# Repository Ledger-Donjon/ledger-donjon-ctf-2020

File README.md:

## Ledger Donjon CTF 2020

This repository lists most of the challenges created for Ledger Donjon CTF 2020.

**This repository will be updated in the next few weeks to add more challenges.**

More information about this CTF can be found on the
[website](https://donjon-ctf.io/). The scoreboard and additional writeups are
available on [CTF Time](https://ctftime.org/event/1173).

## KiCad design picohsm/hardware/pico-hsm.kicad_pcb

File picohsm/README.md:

# picoHSM

## Building and flashing the STM32F205

The firmware for the STM32F205 can be built using CMake:

    cd firmware-mcu
    mkdir build && cd build
    cmake ../src
    make

To flash the microcontroller, be sure the jumpers on the board are configured
properly (JP1 and JP2 on the left), then run:

    make flash

This will flash the board with the default IP and MAC addresses. Other firmwares
with alternate IP and MAC are built by CMake and can be flashed as well:

    make flash11  # For IP ending in .11

## Building and flashing the ATMEGA1284P

The firmware for the ATMEGA1284P can be built using CMake:

    cd firmware-sec
    mkdir build && cd build
    cmake ../src
    make

To flash the microcontroller, connect the Atmel-ICE programmer to the ISP6
connector, and run:

    make flash
    make fuses

Flashing the fuse is important: it configures the microcontroller to use an
external clock (here the clock generated by the STM32F205), which is important
for the third challenge.

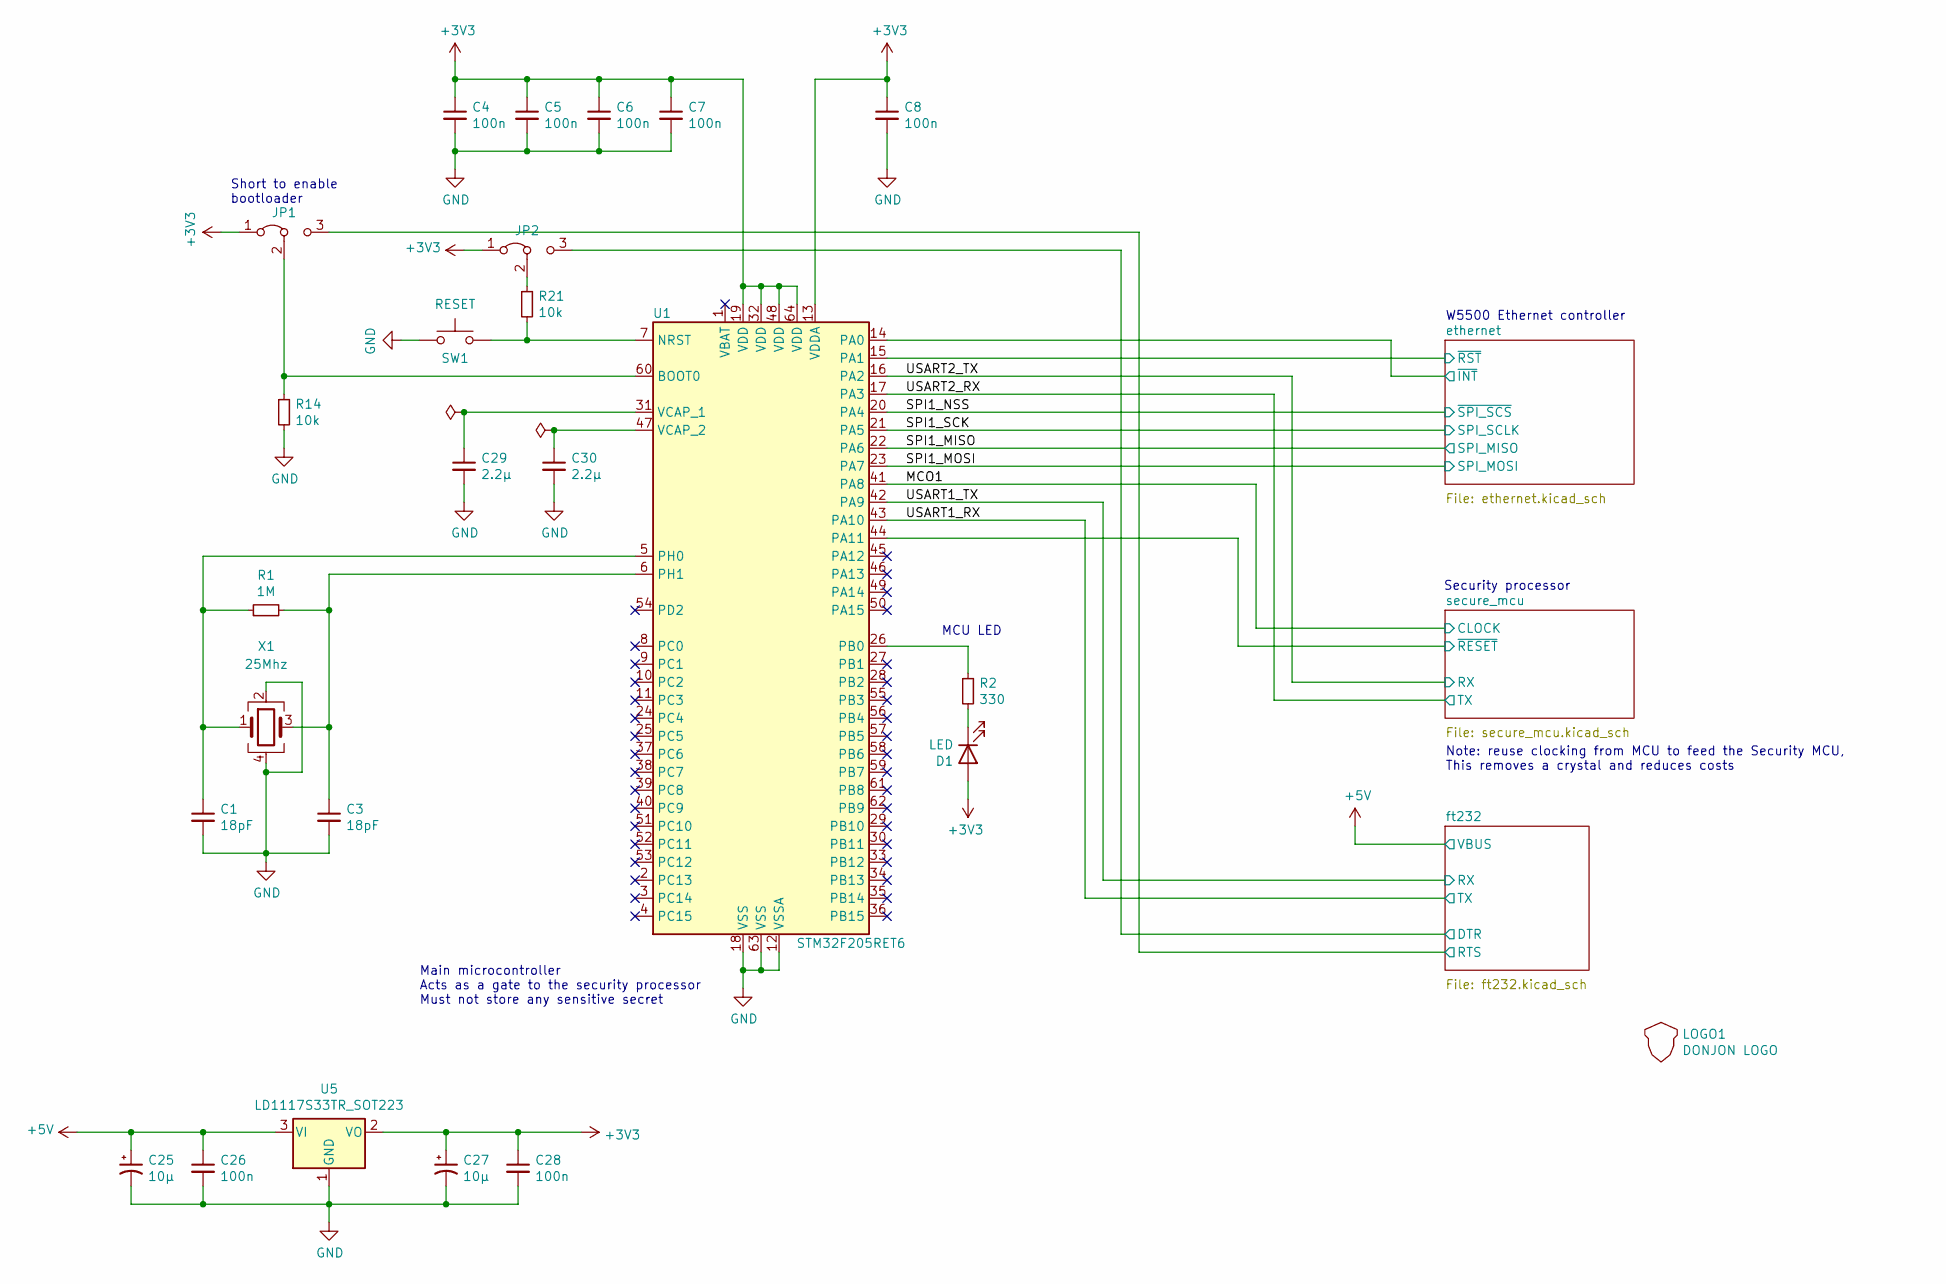
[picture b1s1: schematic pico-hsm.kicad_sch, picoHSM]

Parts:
C1, C3: 18pF; C_0603_1608Metric
C4, C5, C6, C7, C8, C26, C28: 100n; C_0603_1608Metric
C25, C27: 10µ; CP_EIA-3216-10_Kemet-I
C29, C30: 2.2µ; C_0603_1608Metric
D1: LED; D_0603_1608Metric
JP1, JP2: Jumper_3_Bridged12; PinHeader_1x03_P2.54mm_Vertical
LOGO1: DONJON LOGO; donjon-3000
R1: 1M; R_0603_1608Metric
R2: 330; R_0603_1608Metric
R14, R21: 10k; R_0603_1608Metric
SW1: RESET; SW_SPST_B3SL-1022P
U1: STM32F205RET6; LQFP-64_10x10mm_P0.5mm
U5: LD1117S33TR_SOT223; SOT-223-3_TabPin2
X1: 25Mhz; Crystal_SMD_5032-4Pin_5.0x3.2mm

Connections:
+3V3: C4.1, C5.1, C6.1, C7.1, C8.1, C27.1, C28.1, D1.2 (A), JP1.1 (A), JP2.1 (A), U1.13 (VDDA), U1.19 (VDD), U1.32 (VDD), U1.48 (VDD), U1.64 (VDD), U5.2 (VO); also elsewhere on the board
+5V: C25.1, C26.1, U5.3 (VI); also elsewhere on the board
/DTR: JP2.3 (B); also elsewhere on the board
/MCO1: U1.41 (PA8); also elsewhere on the board
/RTS: JP1.3 (B); also elsewhere on the board
/SPI1_MISO: U1.22 (PA6); also elsewhere on the board
/SPI1_MOSI: U1.23 (PA7); also elsewhere on the board
/SPI1_NSS: U1.20 (PA4); also elsewhere on the board
/SPI1_SCK: U1.21 (PA5); also elsewhere on the board
/USART1_RX: U1.43 (PA10); also elsewhere on the board
/USART1_TX: U1.42 (PA9); also elsewhere on the board
/USART2_RX: U1.17 (PA3); also elsewhere on the board
/USART2_TX: U1.16 (PA2); also elsewhere on the board
/~INT: U1.14 (PA0); also elsewhere on the board
/~RESET: U1.44 (PA11); also elsewhere on the board
/~RST: U1.15 (PA1); also elsewhere on the board
GND: C1.2, C3.2, C4.2, C5.2, C6.2, C7.2, C8.2, C25.2, C26.2, C27.2, C28.2, C29.2, C30.2, R14.2, SW1.1, U1.12 (VSSA), U1.18 (VSS), U1.63 (VSS), U5.1 (GND), X1.2, X1.4; also elsewhere on the board
unnamed: C1.1, R1.1, U1.5 (PH0), X1.1
unnamed: C3.1, R1.2, U1.6 (PH1), X1.3
unnamed: C29.1, U1.31 (VCAP_1)
unnamed: C30.1, U1.47 (VCAP_2)
unnamed: D1.1 (K), R2.2
unnamed: JP1.2 (C), R14.1, U1.60 (BOOT0)
unnamed: JP2.2 (C), R21.1
unnamed: R2.1, U1.26 (PB0)
unnamed: R21.2, SW1.2, U1.7 (NRST)

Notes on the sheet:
Short to enable bootloader
Main microcontroller Acts as a gate to the security processor Must not store any sensitive secret
MCU LED
W5500 Ethernet controller
Note: reuse clocking from MCU to feed the Security MCU, This removes a crystal and reduces costs
Security processor

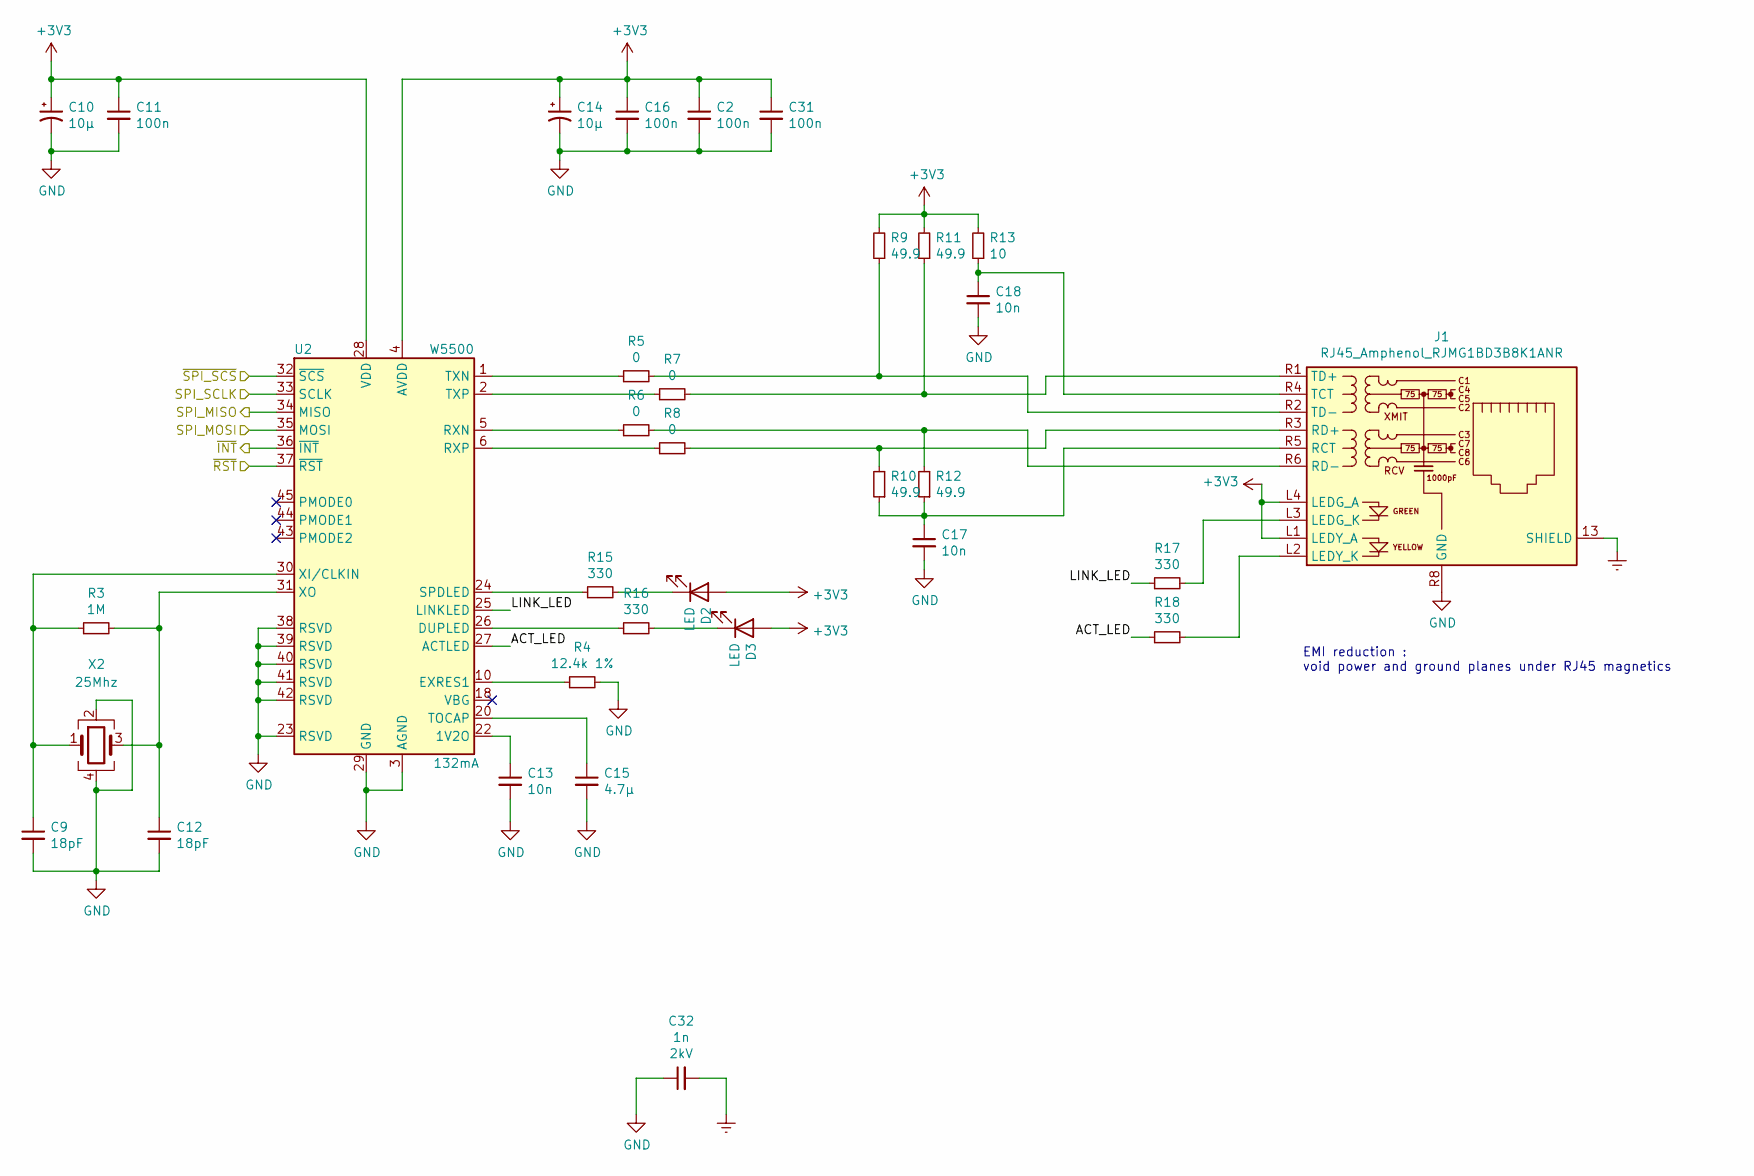
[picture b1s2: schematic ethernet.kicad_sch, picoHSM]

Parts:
C2, C11, C16, C31: 100n; C_0603_1608Metric
C9, C12: 18pF; C_0603_1608Metric
C10, C14: 10µ; CP_EIA-3216-10_Kemet-I
C13, C17, C18: 10n; C_0603_1608Metric
C15: 4.7µ; C_0603_1608Metric
C32: 1n; C_1206_3216Metric_Pad1.42x1.75mm_HandSolder; Voltage 2kV
D2, D3: LED; D_0603_1608Metric
J1: RJ45_Amphenol_RJMG1BD3B8K1ANR
R3: 1M; R_0603_1608Metric
R4: 12.4k 1%; R_0603_1608Metric
R5, R6, R7, R8: 0; R_0603_1608Metric
R9, R10, R11, R12: 49.9; R_0603_1608Metric
R13: 10; R_0603_1608Metric
R15, R16, R17, R18: 330; R_0603_1608Metric
U2: W5500; LQFP-48_7x7mm_P0.5mm
X2: 25Mhz; Crystal_SMD_5032-4Pin_5.0x3.2mm

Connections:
+3V3: C2.1, C10.1, C11.1, C14.1, C16.1, C31.1, D2.2 (A), D3.2 (A), J1.L1 (LEDY_A), J1.L4 (LEDG_A), R9.2, R11.2, R13.2, U2.4 (AVDD), U2.8 (AVDD), U2.11 (AVDD), U2.15 (AVDD), U2.17 (AVDD), U2.21 (AVDD), U2.28 (VDD); also elsewhere on the board
/SPI1_MISO: U2.34 (MISO); also elsewhere on the board
/SPI1_MOSI: U2.35 (MOSI); also elsewhere on the board
/SPI1_NSS: U2.32 (~SCS); also elsewhere on the board
/SPI1_SCK: U2.33 (SCLK); also elsewhere on the board
/ethernet/ACT_LED: R18.1, U2.27 (ACTLED)
/ethernet/LINK_LED: R17.1, U2.25 (LINKLED)
/~INT: U2.36 (~INT); also elsewhere on the board
/~RST: U2.37 (~RST); also elsewhere on the board
Earth: C32.2, J1.13 (SHIELD)
GND: C2.2, C9.2, C10.2, C11.2, C12.2, C13.2, C14.2, C15.2, C16.2, C17.2, C18.2, C31.2, C32.1, J1.R8 (GND), R4.2, U2.3 (AGND), U2.9 (AGND), U2.14 (AGND), U2.16 (AGND), U2.19 (AGND), U2.23 (RSVD), U2.29 (GND), U2.38 (RSVD), U2.39 (RSVD), U2.40 (RSVD), U2.41 (RSVD), U2.42 (RSVD), U2.48 (AGND), X2.2, X2.4; also elsewhere on the board
unnamed: C9.1, R3.1, U2.30 (XI/CLKIN), X2.1
unnamed: C12.1, R3.2, U2.31 (XO), X2.3
unnamed: C13.1, U2.22 (1V2O)
unnamed: C15.1, U2.20 (TOCAP)
unnamed: C17.1, J1.R5 (RCT), R10.1, R12.1
unnamed: C18.1, J1.R4 (TCT), R13.1
unnamed: D2.1 (K), R15.2
unnamed: D3.1 (K), R16.2
unnamed: J1.L2 (LEDY_K), R18.2
unnamed: J1.L3 (LEDG_K), R17.2
unnamed: J1.R1 (TD+), R7.2, R11.1
unnamed: J1.R2 (TD-), R5.2, R9.1
unnamed: J1.R3 (RD+), R8.2, R10.2
unnamed: J1.R6 (RD-), R6.2, R12.2
unnamed: R4.1, U2.10 (EXRES1)
unnamed: R5.1, U2.1 (TXN)
unnamed: R6.1, U2.5 (RXN)
unnamed: R7.1, U2.2 (TXP)
unnamed: R8.1, U2.6 (RXP)
unnamed: R15.1, U2.24 (SPDLED)
unnamed: R16.1, U2.26 (DUPLED)

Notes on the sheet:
EMI reduction : void power and ground planes under RJ45 magnetics

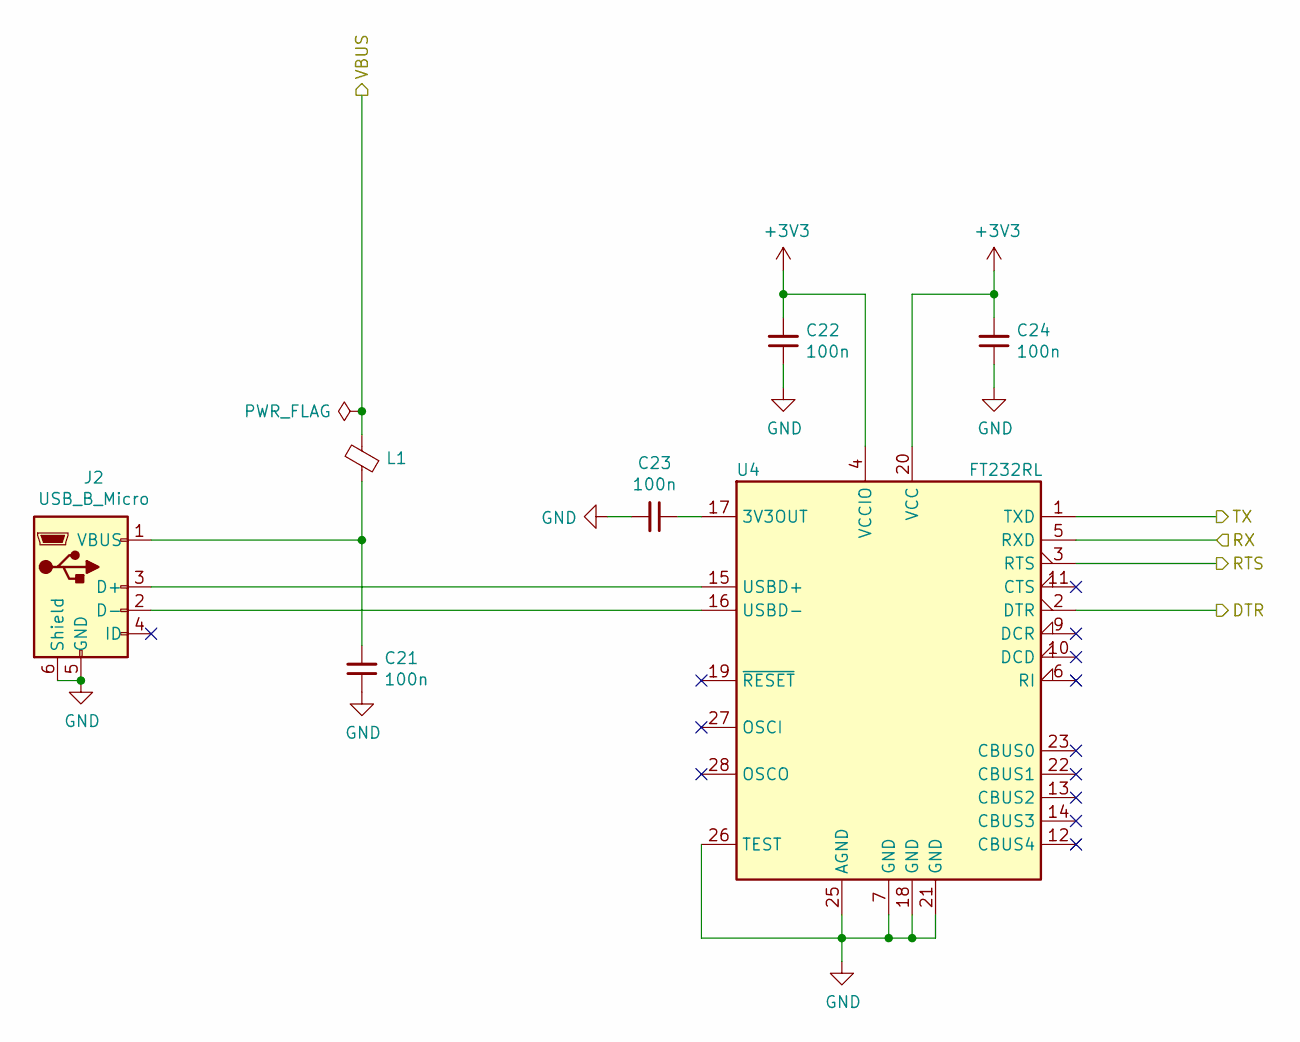
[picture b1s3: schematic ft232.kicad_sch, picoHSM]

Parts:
C21, C22, C23, C24: 100n; C_0603_1608Metric
J2: USB_B_Micro; USB_Micro-B_Wuerth_629105150521
L1: Ferrite_Bead_Small; L_0603_1608Metric
U4: FT232RL; SSOP-28_5.3x10.2mm_P0.65mm

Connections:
+3V3: C22.2, C24.2, U4.4 (VCCIO), U4.20 (VCC); also elsewhere on the board
+5V: L1.2; also elsewhere on the board
/DTR: U4.2 (DTR); also elsewhere on the board
/RTS: U4.3 (RTS); also elsewhere on the board
/USART1_RX: U4.1 (TXD); also elsewhere on the board
/USART1_TX: U4.5 (RXD); also elsewhere on the board
GND: C21.1, C22.1, C23.2, C24.1, J2.5 (GND), J2.6 (Shield), U4.7 (GND), U4.18 (GND), U4.21 (GND), U4.25 (AGND), U4.26 (TEST); also elsewhere on the board
unnamed: C21.2, J2.1 (VBUS), L1.1
unnamed: C23.1, U4.17 (3V3OUT)
unnamed: J2.2 (D-), U4.16 (USBD-)
unnamed: J2.3 (D+), U4.15 (USBD+)

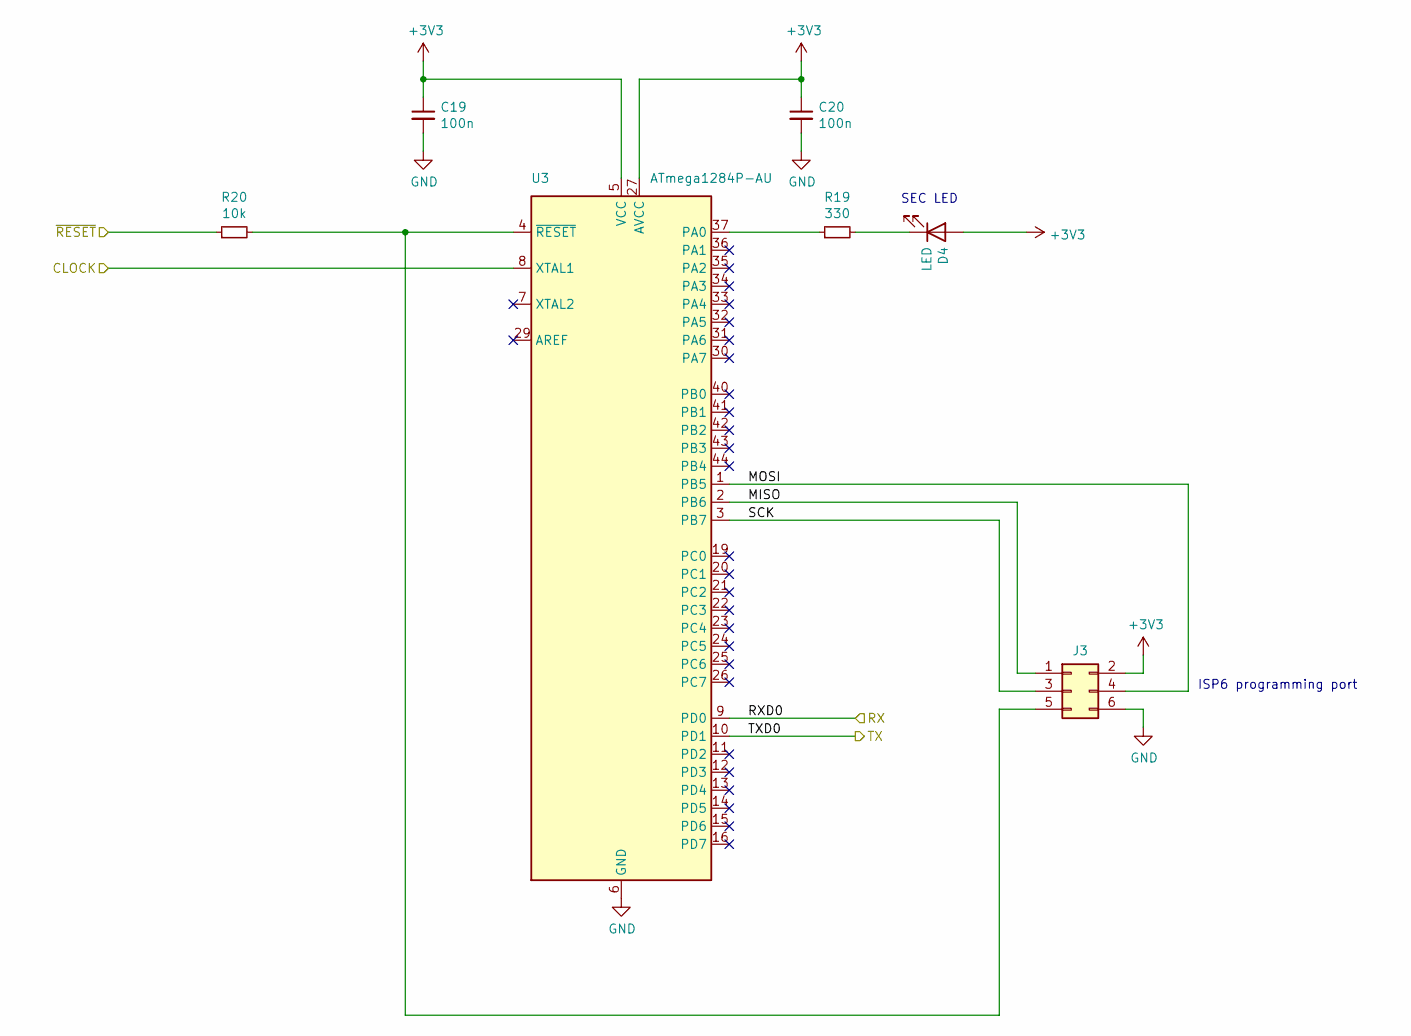
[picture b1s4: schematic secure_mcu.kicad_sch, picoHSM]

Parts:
C19, C20: 100n; C_0603_1608Metric
D4: LED; D_0603_1608Metric
J3: Conn_02x03_Odd_Even; PinHeader_2x03_P2.54mm_Vertical
R19: 330; R_0603_1608Metric
R20: 10k; R_0603_1608Metric
U3: ATmega1284P-AU; TQFP-44_10x10mm_P0.8mm

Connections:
+3V3: C19.1, C20.1, D4.2 (A), J3.2, U3.5 (VCC), U3.17 (VCC), U3.27 (AVCC), U3.38 (VCC); also elsewhere on the board
/MCO1: U3.8 (XTAL1); also elsewhere on the board
/USART2_RX: U3.10 (PD1); also elsewhere on the board
/USART2_TX: U3.9 (PD0); also elsewhere on the board
/secure_mcu/MISO: J3.1, U3.2 (PB6)
/secure_mcu/MOSI: J3.4, U3.1 (PB5)
/secure_mcu/SCK: J3.3, U3.3 (PB7)
/~RESET: R20.1; also elsewhere on the board
GND: C19.2, C20.2, J3.6, U3.6 (GND), U3.18 (GND), U3.28 (GND), U3.39 (GND); also elsewhere on the board
unnamed: D4.1 (K), R19.2
unnamed: J3.5, R20.2, U3.4 (~RESET)
unnamed: R19.1, U3.37 (PA0)

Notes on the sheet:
SEC LED
ISP6 programming port

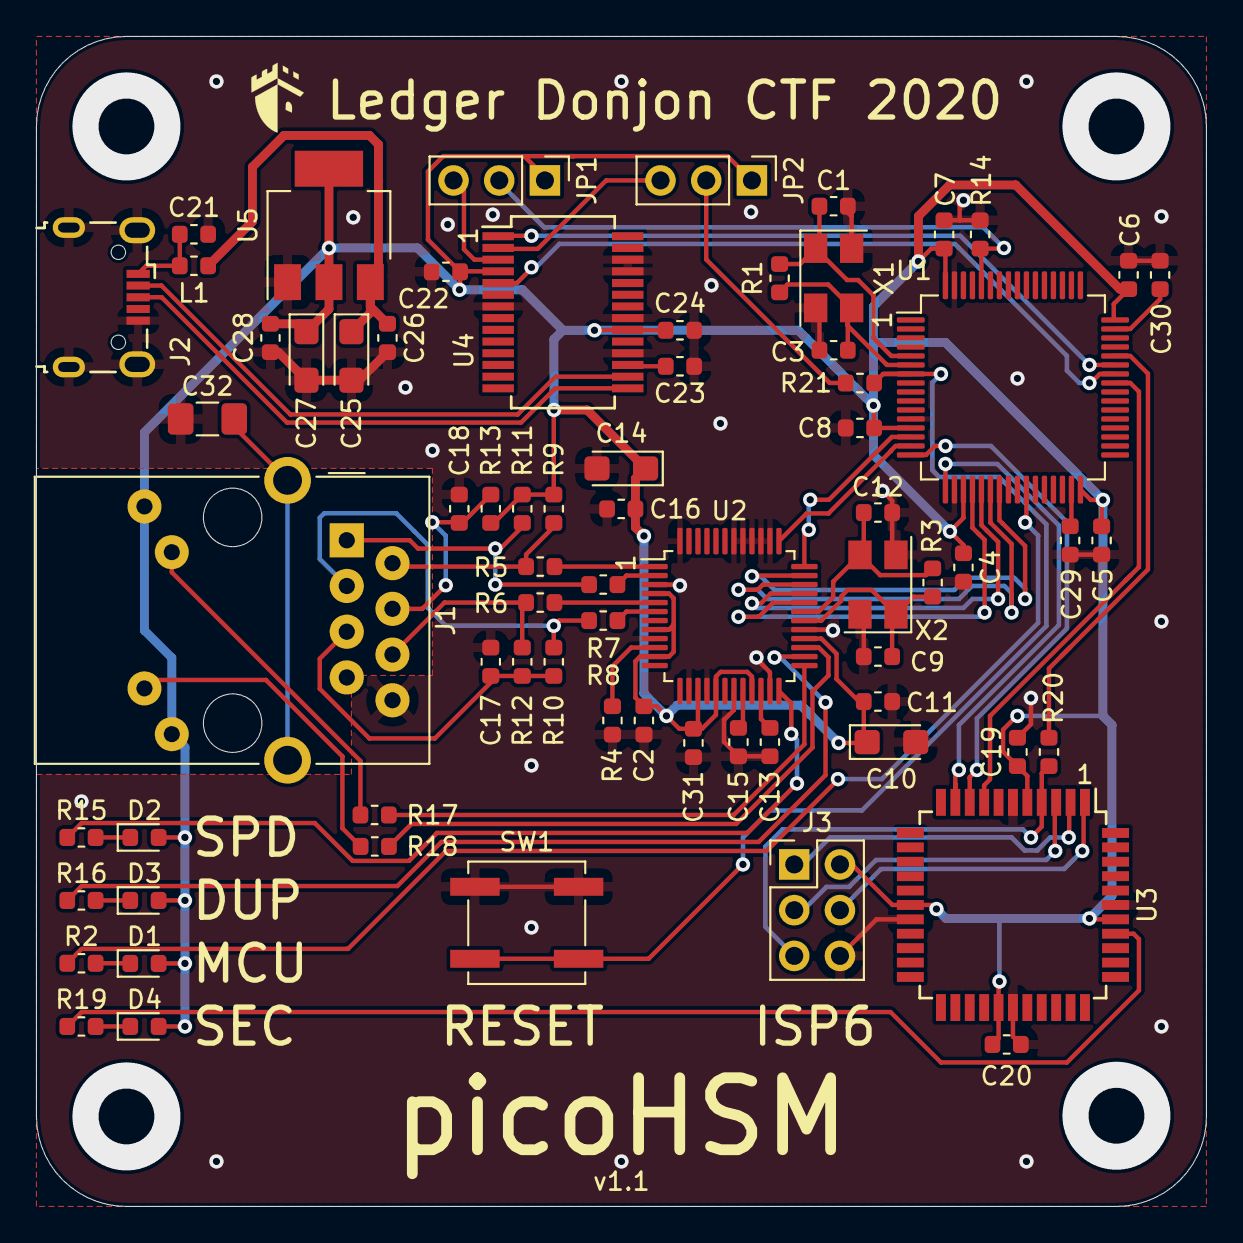
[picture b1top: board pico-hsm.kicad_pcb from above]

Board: 2 copper layers, 65.0 x 65.0 mm, 72 parts (0 on the bottom side), 60 nets.

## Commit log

2020-11-30 add ghostbuster
2020-11-30 ghostbuster: rename attacker/ to exploit/
2020-12-01 add README
2020-12-01 ghostbuster: add libcheck.so
2020-12-04 Add Modern Cryptocomputer and SMPC Signature challenges
2020-12-15 add picoHSM
2021-11-16 Add "Elliptic Relations"
